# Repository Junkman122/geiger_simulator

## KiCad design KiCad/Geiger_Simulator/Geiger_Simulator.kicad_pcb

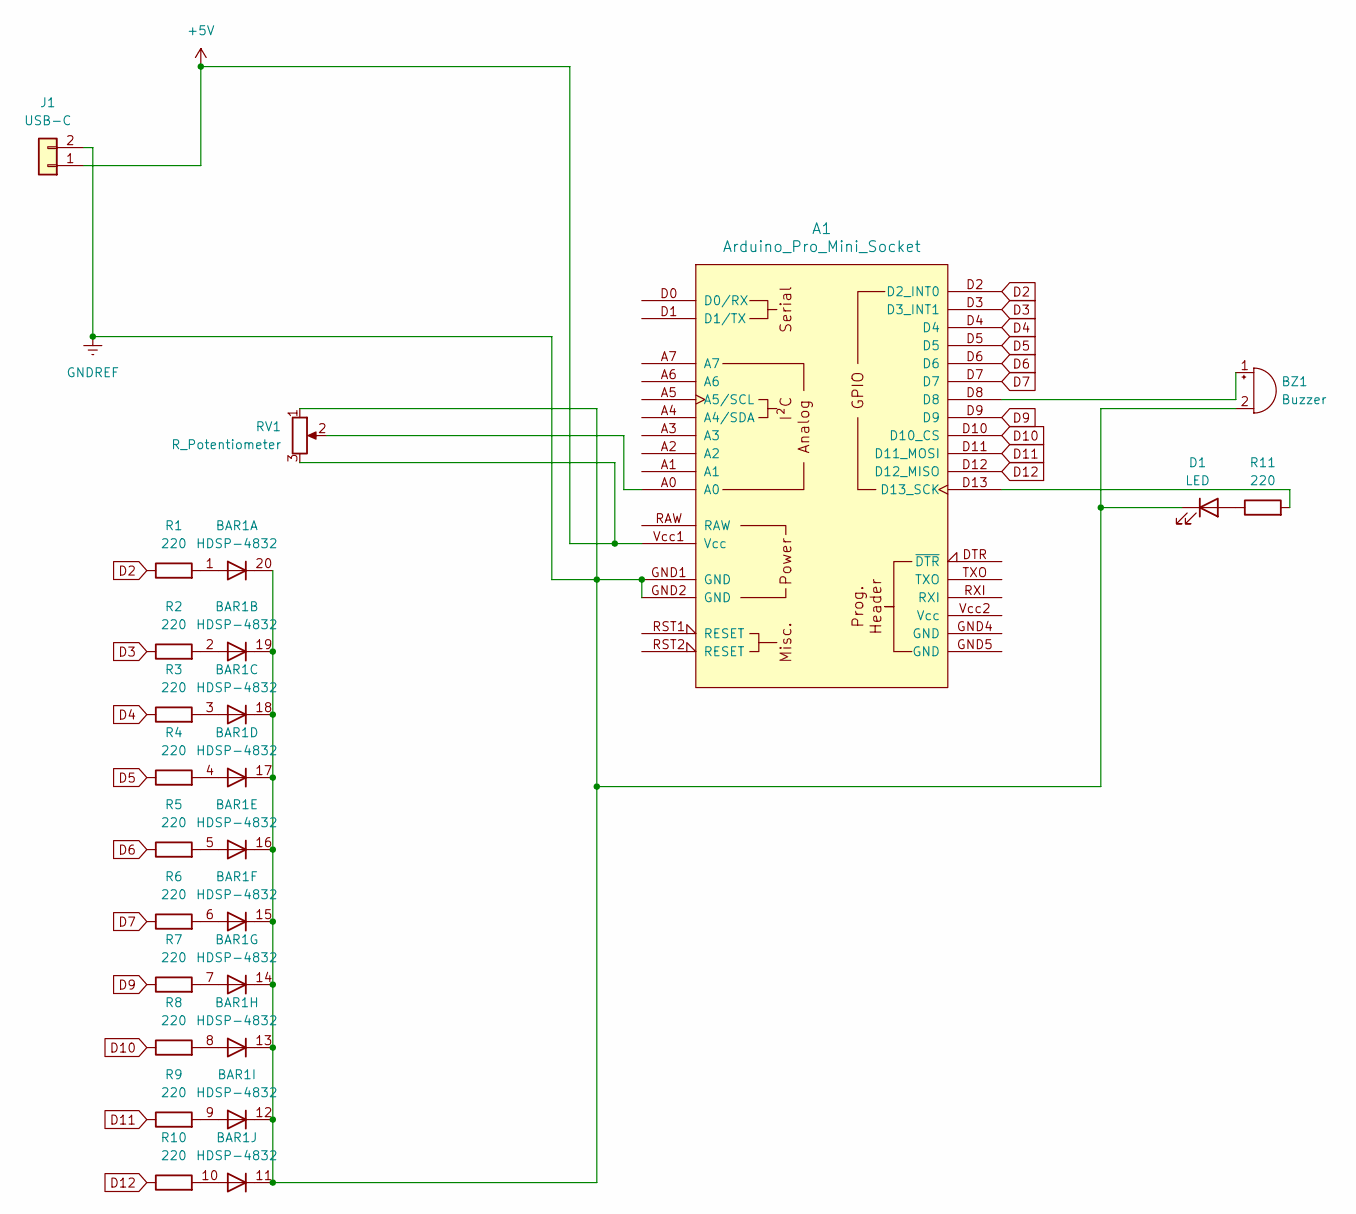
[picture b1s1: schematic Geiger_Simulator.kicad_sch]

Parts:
A1: Arduino_Pro_Mini_Socket
BAR1: HDSP-4832
BZ1: Buzzer; Buzzer_12x9.5RM7.6
D1: LED; LED_D3.0mm
J1: USB-C; PinHeader_1x02_P2.54mm_Vertical
R1, R2, R3, R4, R5, R6, R7, R8, R9, R10, R11: 220; R_Axial_DIN0207_L6.3mm_D2.5mm_P10.16mm_Horizontal
RV1: R_Potentiometer; PinHeader_1x03_P2.54mm_Vertical

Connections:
+5V: A1.Vcc1 (Vcc), J1.1, RV1.3
D2: A1.D2 (D2_INT0), R1.1
D3: A1.D3 (D3_INT1), R2.1
D4: A1.D4, R3.1
D5: A1.D5, R4.1
D6: A1.D6, R5.1
D7: A1.D7, R6.1
D9: A1.D9, R7.1
D10: A1.D10 (D10_CS), R8.1
D11: A1.D11 (D11_MOSI), R9.1
D12: A1.D12 (D12_MISO), R10.1
GNDREF: A1.GND1 (GND), A1.GND2 (GND), BAR1.11 (K), BAR1.12 (K), BAR1.13 (K), BAR1.14 (K), BAR1.15 (K), BAR1.16 (K), BAR1.17 (K), BAR1.18 (K), BAR1.19 (K), BAR1.20 (K), BZ1.2 (-), D1.1 (K), J1.2, RV1.1
unnamed: A1.D13 (D13_SCK), R11.2
unnamed: A1.A0, RV1.2
unnamed: BAR1.1 (A), R1.2
unnamed: BAR1.2 (A), R2.2
unnamed: BAR1.3 (A), R3.2
unnamed: BAR1.4 (A), R4.2
unnamed: BAR1.5 (A), R5.2
unnamed: BAR1.6 (A), R6.2
unnamed: BAR1.7 (A), R7.2
unnamed: BAR1.8 (A), R8.2
unnamed: BAR1.9 (A), R9.2
unnamed: BAR1.10 (A), R10.2
unnamed: A1.D8, BZ1.1 (+)
unnamed: D1.2 (A), R11.1

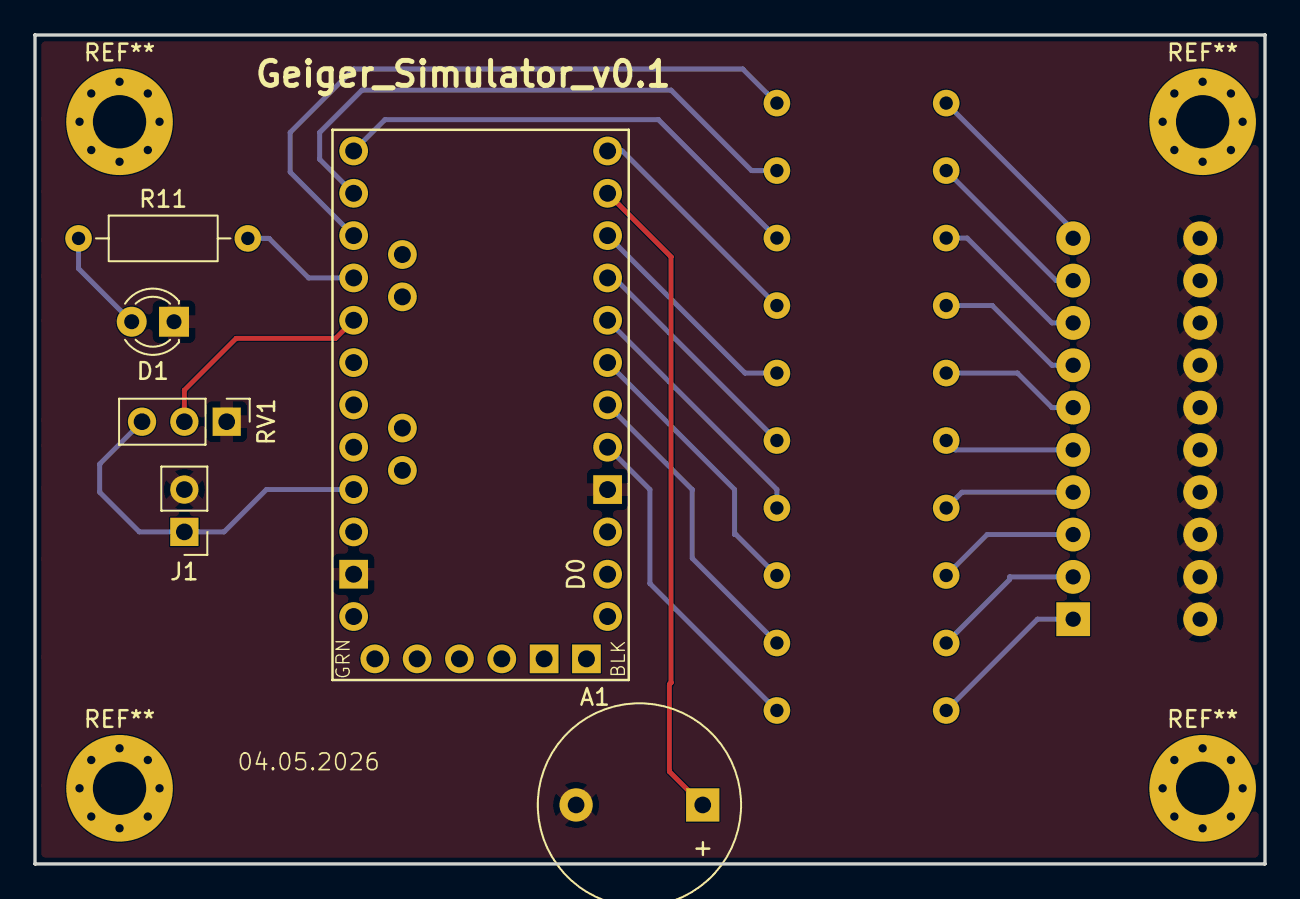
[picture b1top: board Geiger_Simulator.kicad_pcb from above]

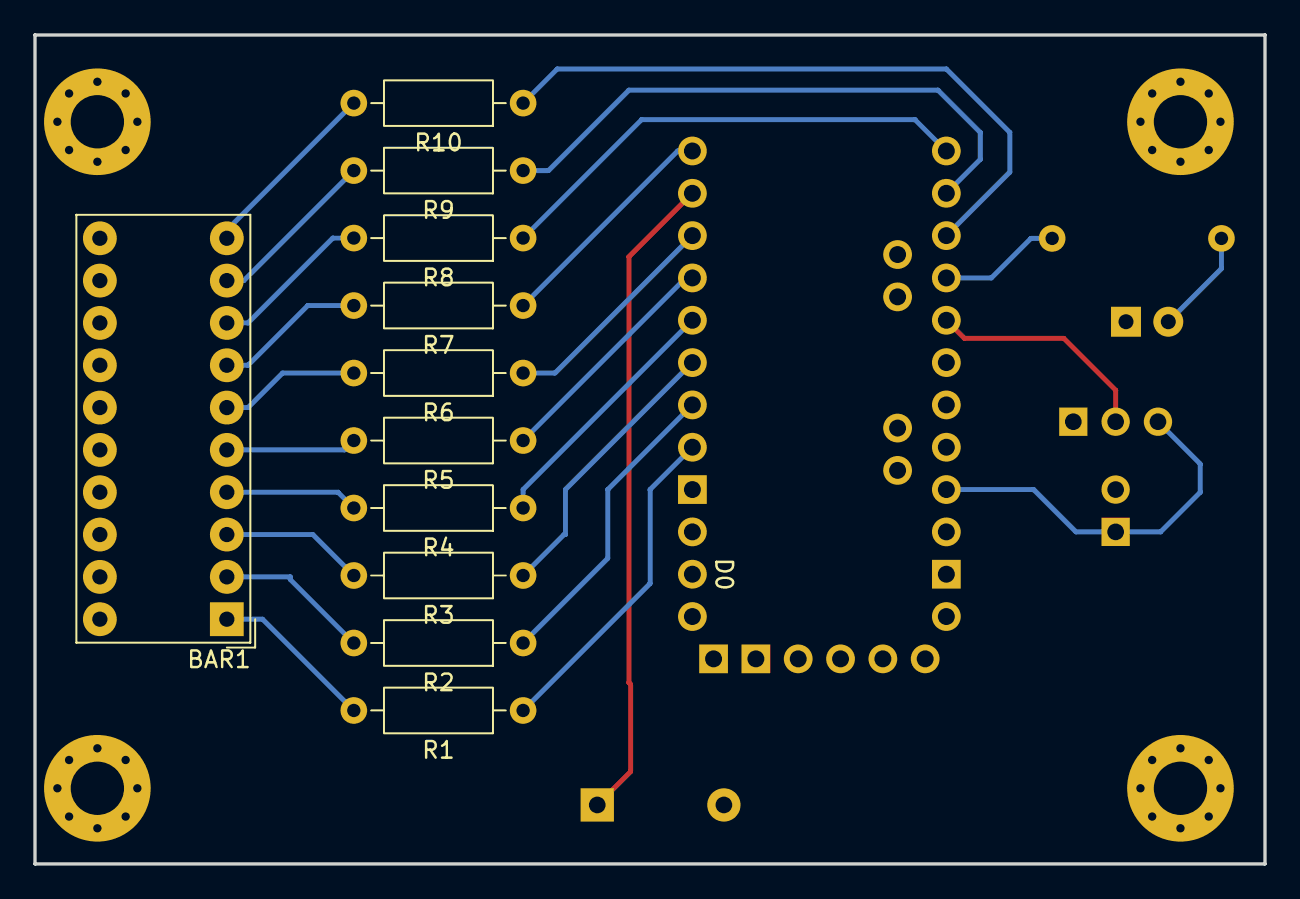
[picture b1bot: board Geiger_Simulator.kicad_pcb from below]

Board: 2 copper layers, 73.8 x 49.7 mm, 17 parts (11 on the bottom side), 26 nets.

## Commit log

2026-05-18 new 3D files
